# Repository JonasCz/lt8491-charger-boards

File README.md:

# LT8491 MPPT boosting solar charge controller mainboard

**PCB layout**:

**Description**: This project started out with the goal of reimplementing [Craig Peacock's design](https://circuitmaker.com/Projects/Details/Craig-Peacock-4/LT8490-Buck-Boost-Multi-Chemistry-Battery-Charger-with-MPPT) in KiCad, while also making it more compact;

**Status**: Test PCB assembled: LT8491 starts and communicates over i2C, but performance is unusably poor. Unsure why.

**Features**:

* Auxilary switching power supply to power additional future display board, can be enabled/disabled at runtime for power saving
* As compact as possible while keeping the board single sided
* High performance and efficiency (hopefully)
* XT60 connectors
* 60v max in and out

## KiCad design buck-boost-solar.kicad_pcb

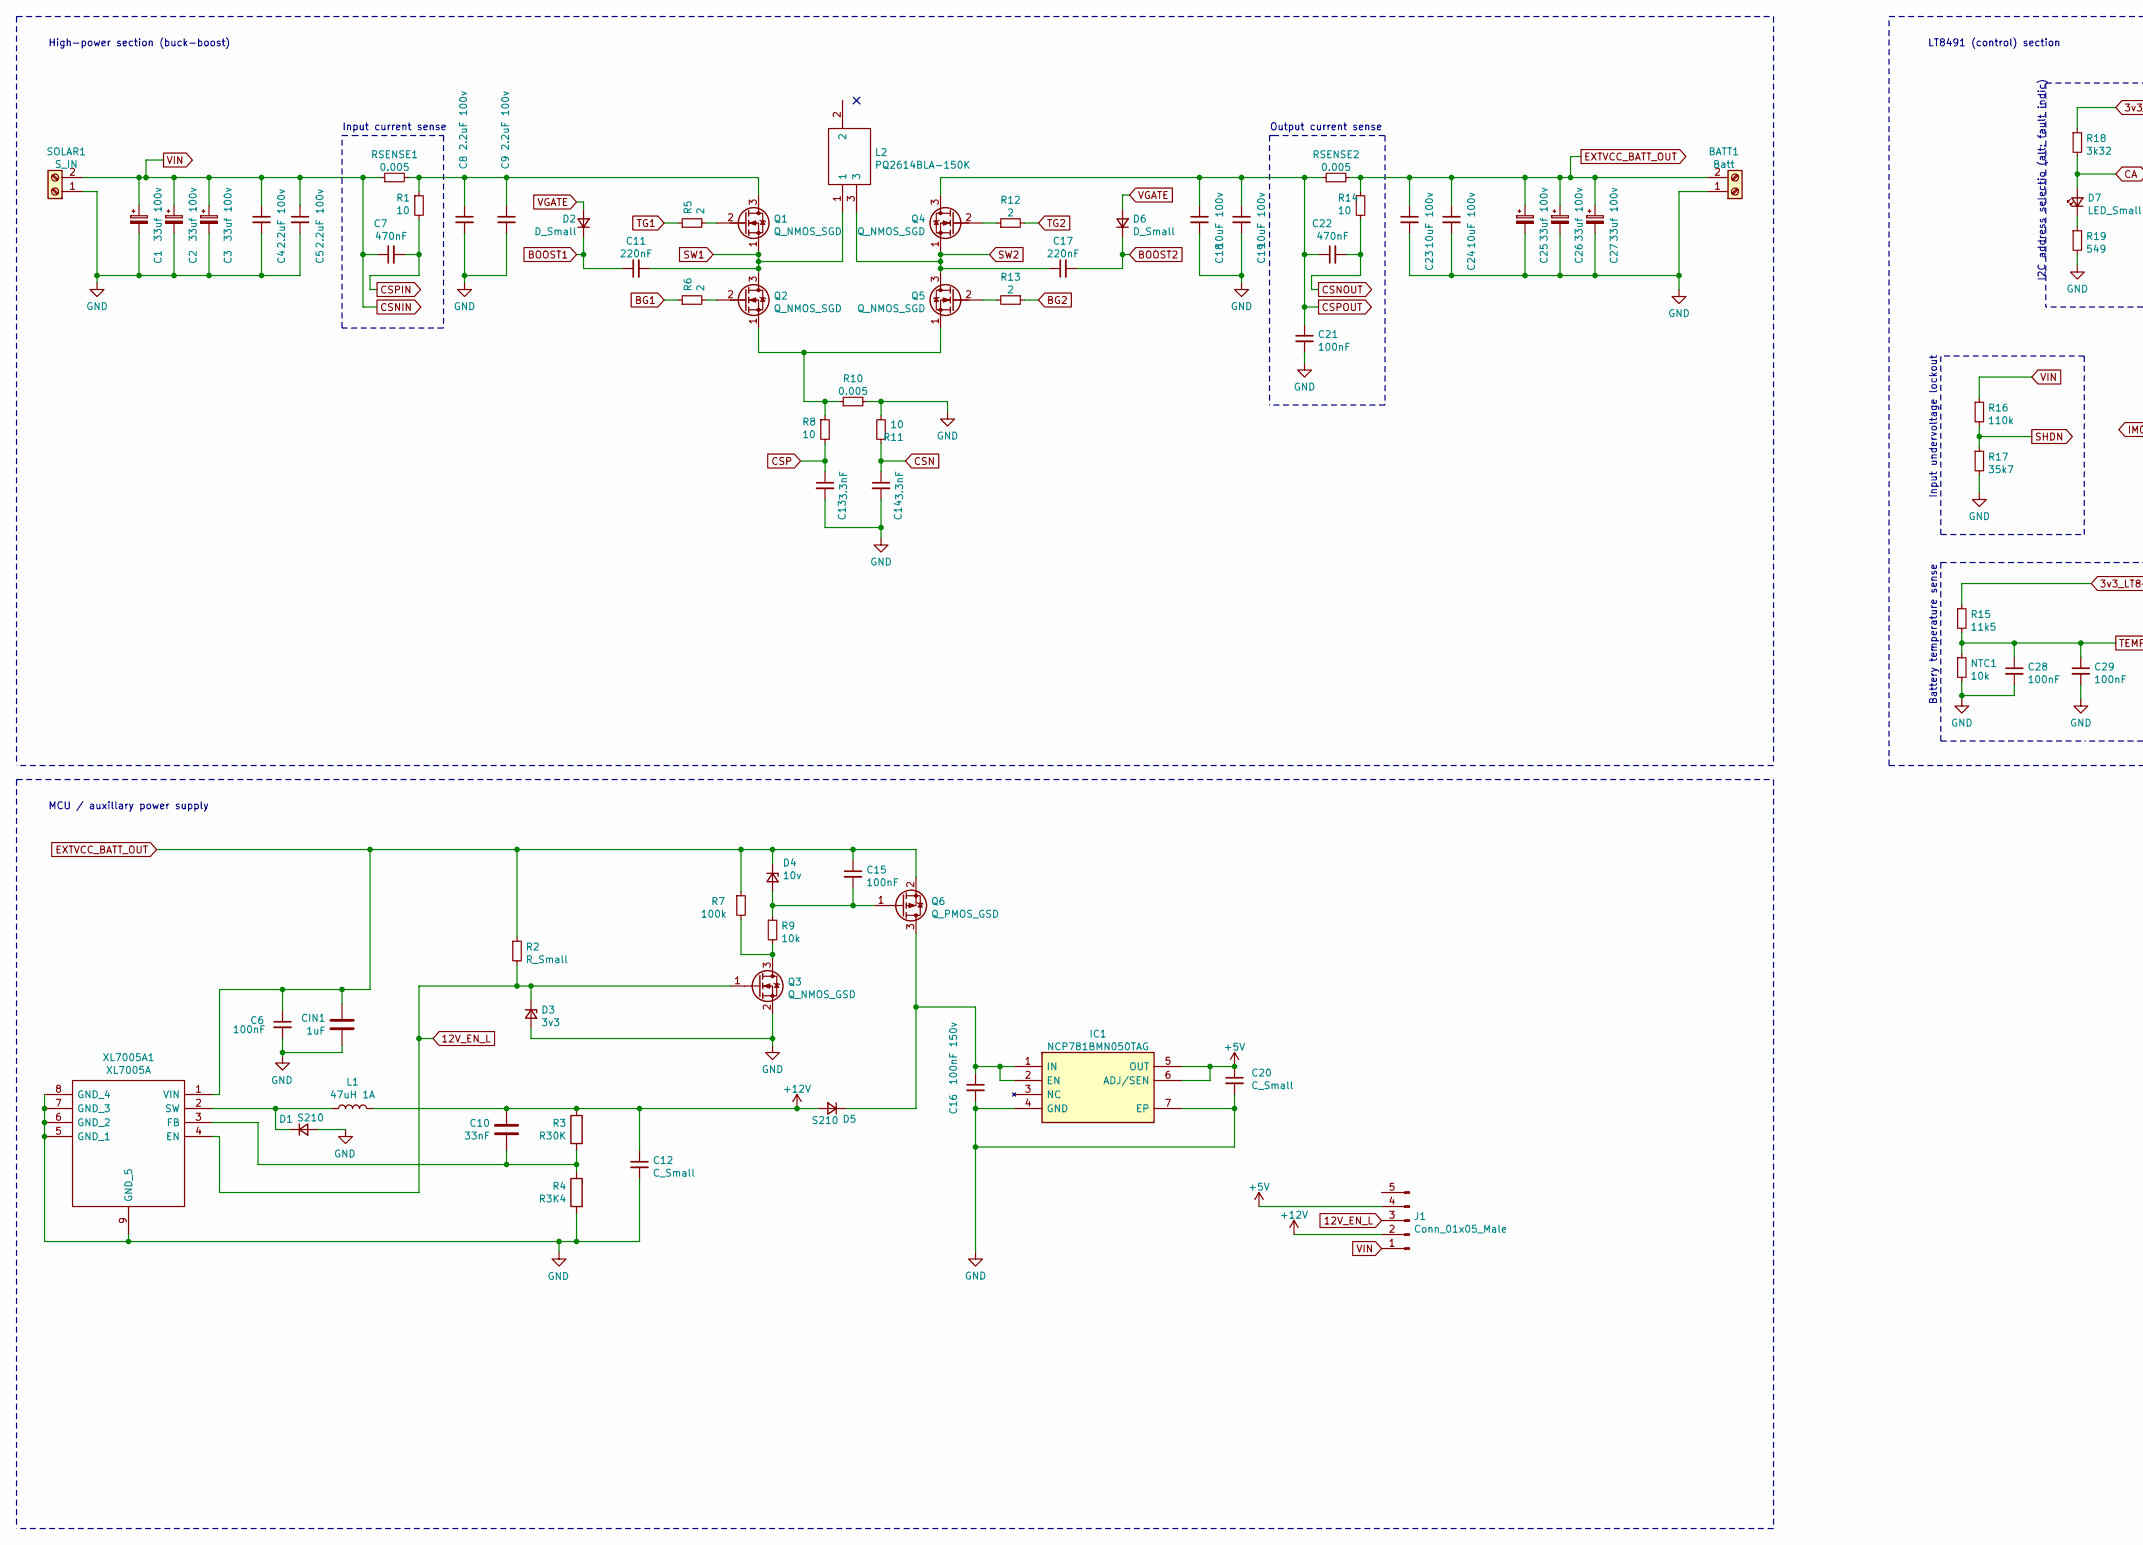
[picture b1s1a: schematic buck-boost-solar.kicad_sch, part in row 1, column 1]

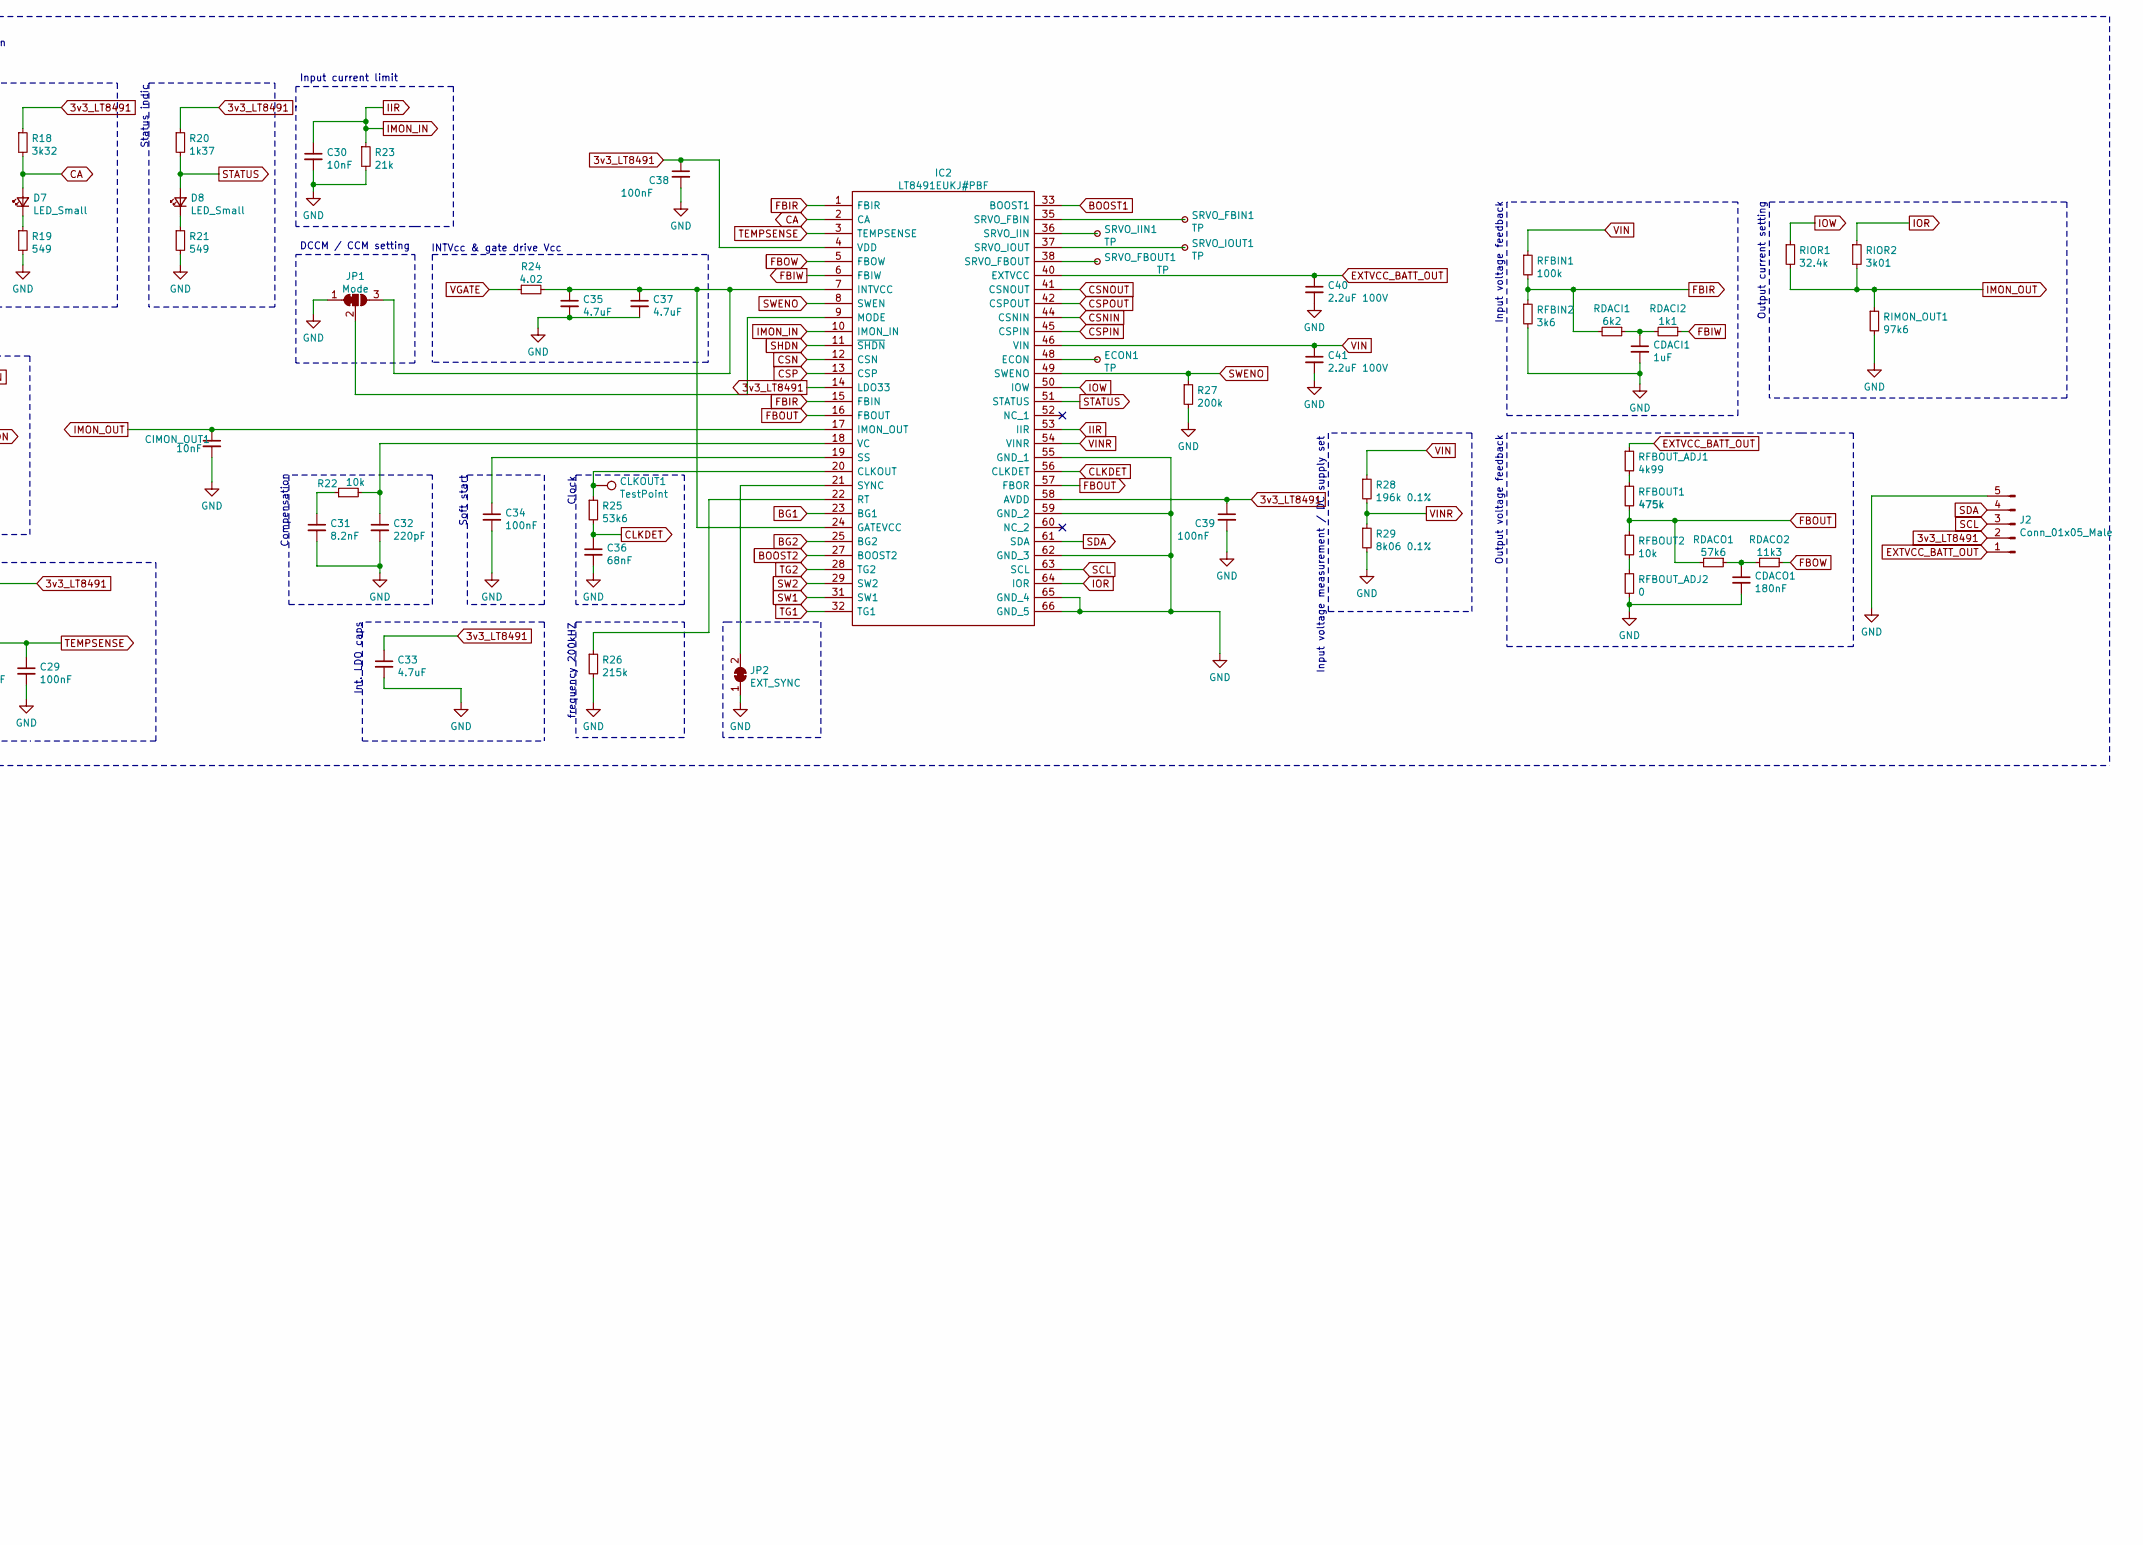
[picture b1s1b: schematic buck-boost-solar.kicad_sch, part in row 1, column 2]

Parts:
BATT1: Batt; Amass_XT60PW-M_Kombifootprint; LCSC Part Number C98732
C1, C2, C3, C25, C26, C27: 33uf 100v; CP_Radial_D10.0mm_P5.00mm; LCSC Part Number C407997
C4, C5, C8, C9: 2.2uF 100v; C_1210_3225Metric; LCSC Part Number C338133
C6, C21, C28, C29, C34, C38, C39: 100nF; C_0603_1608Metric; LCSC Part Number C696916
C7, C22: 470nF; C_0603_1608Metric; LCSC Part Number C1623
C10: 33nF; C_0603_1608Metric
C11, C17: 220nF; C_0603_1608Metric; LCSC Part Number C335532
C12: C_Small; C_1210_3225Metric
C13, C14: 3.3nF; C_0603_1608Metric; LCSC Part Number C482476
C15: 100nF; C_0603_1608Metric
C16: 100nF 150v; C_1206_3216Metric
C18, C19, C23, C24: 10uF 100v; C_2220_5650Metric; LCSC Part Number C153035
C20: C_Small; C_0603_1608Metric
C30: 10nF; C_0603_1608Metric; LCSC Part Number C100042
C31: 8.2nF; C_0603_1608Metric; LCSC Part Number C376849
C32: 220pF; C_0603_1608Metric; LCSC Part Number C376820
C33, C35, C37: 4.7uF; C_0603_1608Metric; LCSC Part Number C69335
C36: 68nF; C_0603_1608Metric; LCSC Part Number C237232
C40, C41: 2.2uF 100V; C_1210_3225Metric; LCSC Part Number C338133
CDACI1: 1uF; C_0603_1608Metric; LCSC Part Number C5673
CDACO1: 180nF; C_0603_1608Metric; LCSC Part Number C519442
CIMON_OUT1: 10nF; C_0603_1608Metric; LCSC Part Number C100042
CIN1: 1uF; C_1206_3216Metric
CLKOUT1: TestPoint; TestPoint_Pad_D1.0mm
D1, D5: S210; D_SOD-123
D2, D6: D_Small; D_SOD-123; LCSC Part Number C258207
D3: 3v3; D_SOD-123
D4: 10v; D_SOD-123
D7, D8: LED_Small; D_0805_2012Metric; LCSC Part Number C72037
ECON1: TP; TestPoint_Pad_D1.0mm
IC1: NCP781BMN050TAG; Manufacturer_Part_Number NCP781BMN050TAG; Mouser Part Number 863-NCP781BMN050TAG
IC2: LT8491EUKJ#PBF; LT8491EUKJ; Manufacturer_Part_Number LT8491EUKJ#PBF; Mouser Part Number 584-LT8491EUKJ#PBF
J1, J2: Conn_01x05_Male; PinHeader_1x05_P2.54mm_Vertical
JP1: Mode; SolderJumper-3_P1.3mm_Bridged2Bar12_RoundedPad1.0x1.5mm
JP2: EXT_SYNC; SolderJumper-2_P1.3mm_Bridged_RoundedPad1.0x1.5mm
L1: 47uH 1A; L_7.3x7.3_H4.5
L2: PQ2614BLA-150K; PQ2614BLA100K; Manufacturer_Part_Number PQ2614BLA-150K; Mouser Part Number 652-PQ2614BLA-150K
NTC1: 10k; R_0805_2012Metric; LCSC Part Number C338623
Q1, Q2, Q4, Q5: Q_NMOS_SGD; TDSON-8-1-SGD; LCSC Part Number C148260
Q3: Q_NMOS_GSD; SOT-23; LCSC Part Number C397175
Q6: Q_PMOS_GSD; SOT-23; LCSC Part Number C700960
R1, R8, R11, R14: 10; R_0603_1608Metric; LCSC Part Number C384297
R2: R_Small; R_0603_1608Metric
R3: R30K; R_0603_1608Metric
R4: R3K4; R_0603_1608Metric
R5, R6, R12, R13: 2; R_0603_1608Metric; LCSC Part Number C286596
R7: 100k; R_0603_1608Metric
R9: 10k; R_0603_1608Metric
R10: 0.005; R_2512_6332Metric; LCSC Part Number C457120
R15: 11k5; R_0603_1608Metric; LCSC Part Number C25949
R16: 110k; R_0603_1608Metric; LCSC Part Number C25805
R17: 35k7; R_0603_1608Metric; LCSC Part Number C23027
R18: 3k32; R_0603_1608Metric; LCSC Part Number C321860
R19, R21: 549; R_0603_1608Metric; LCSC Part Number C23079
R20: 1k37; R_0603_1608Metric; LCSC Part Number C22839
R22: 10k; R_0603_1608Metric; LCSC Part Number C25804
R23: 21k; R_0603_1608Metric; LCSC Part Number C22956
R24: 4.02; R_0603_1608Metric; LCSC Part Number C322168
R25: 53k6; R_0603_1608Metric; LCSC Part Number C23074
R26: 215k; R_0603_1608Metric; LCSC Part Number C22954
R27: 200k; R_0603_1608Metric; LCSC Part Number C304068
R28: 196k 0.1%; R_0603_1608Metric; LCSC Part Number C705733
R29: 8k06 0.1%; R_0603_1608Metric; LCSC Part Number C304068
RDACI1: 6k2; R_0603_1608Metric; LCSC Part Number C319499
RDACI2: 1k1; R_0603_1608Metric; LCSC Part Number C351674
RDACO1: 57k6; R_0603_1608Metric; LCSC Part Number C243028
RDACO2: 11k3; R_0603_1608Metric; LCSC Part Number C491110
RFBIN1: 100k; R_0603_1608Metric; LCSC Part Number C335088
RFBIN2: 3k6; R_0603_1608Metric; LCSC Part Number C318132
RFBOUT1: 475k; R_0603_1608Metric; LCSC Part Number C503464
RFBOUT2: 10k; R_0603_1608Metric; LCSC Part Number C309083
RFBOUT_ADJ1: 4k99; R_0603_1608Metric; LCSC Part Number C335079
RFBOUT_ADJ2: 0; R_0603_1608Metric; LCSC Part Number C286596
RIMON_OUT1: 97k6; R_0603_1608Metric; LCSC Part Number C23269
RIOR1: 32.4k; R_0603_1608Metric; LCSC Part Number C170561
RIOR2: 3k01; R_0603_1608Metric; LCSC Part Number C168308
RSENSE1, RSENSE2: 0.005; R_2512_6332Metric; LCSC Part Number C457120
SOLAR1: S_IN; Amass_XT60PW-M_Kombifootprint; LCSC Part Number C428722
SRVO_FBIN1: TP; TestPoint_Pad_D1.0mm
SRVO_FBOUT1: TP; TestPoint_Pad_D1.0mm
SRVO_IIN1: TP; TestPoint_Pad_D1.0mm
SRVO_IOUT1: TP; TestPoint_Pad_D1.0mm
XL7005A1: XL7005A; SOIC127P600X175-9N; Manufacturer_Part_Number XL7005A; LCSC Part Number C50848

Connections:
3v3_LT8491: C33.1, C38.1, C39.1, IC2.4 (VDD), IC2.14 (LDO33), IC2.58 (AVDD), J2.2, R15.1, R18.1, R20.1
12V_EN_L: D3.1 (K), J1.3, Q3.1 (G), R2.2, XL7005A1.4 (EN)
+5V: C20.1, IC1.5 (OUT), IC1.6 (ADJ/SEN), J1.4
+12V: C10.1, C12.1, D5.2 (A), J1.2, L1.1, R3.1
BG1: IC2.23 (BG1), R6.1
BG2: IC2.25 (BG2), R13.1
BOOST1: C11.1, D2.1 (K), IC2.33 (BOOST1)
BOOST2: C17.2, D6.1 (K), IC2.27 (BOOST2)
CA: D7.2 (A), IC2.2 (CA), R18.2
CLKDET: C36.1, IC2.56 (CLKDET), R25.2
CSN: C14.1, IC2.12 (CSN), R11.1
CSNIN: C1.1, C2.1, C3.1, C4.1, C5.1, C7.1, C41.1, IC2.44 (CSNIN), IC2.46 (VIN), J1.1, R16.1, R28.1, RFBIN1.1, RSENSE1.1, SOLAR1.2
CSNOUT: C22.2, IC2.41 (CSNOUT), R14.2
CSP: C13.1, IC2.13 (CSP), R8.2
CSPIN: C7.2, IC2.45 (CSPIN), R1.2
CSPOUT: C18.1, C19.1, C21.1, C22.1, IC2.42 (CSPOUT), Q4.3 (D), RSENSE2.1
EXTVCC_BATT_OUT: BATT1.2, C6.1, C15.1, C23.1, C24.1, C25.1, C26.1, C27.1, C40.1, CIN1.1, D4.1 (K), IC2.40 (EXTVCC), J2.1, Q6.2 (S), R2.1, R7.1, R14.1, RFBOUT_ADJ1.1, RSENSE2.2, XL7005A1.1 (VIN)
FBIR: IC2.1 (FBIR), IC2.15 (FBIN), RDACI1.2, RFBIN1.2, RFBIN2.1
FBIW: IC2.6 (FBIW), RDACI2.1
FBOUT: IC2.16 (FBOUT), IC2.57 (FBOR), RDACO1.2, RFBOUT1.2, RFBOUT2.1
FBOW: IC2.5 (FBOW), RDACO2.1
GND: BATT1.1, C1.2, C2.2, C3.2, C4.2, C5.2, C6.2, C8.2, C9.2, C12.2, C13.2, C14.2, C16.2, C18.2, C19.2, C20.2, C21.2, C23.2, C24.2, C25.2, C26.2, C27.2, C28.2, C29.2, C30.2, C31.2, C32.2, C33.2, C34.2, C35.2, C36.2, C37.2, C38.2, C39.2, C40.2, C41.2, CDACI1.2, CDACO1.2, CIMON_OUT1.2, CIN1.2, D1.2 (A), D3.2 (A), IC1.4 (GND), IC1.7 (EP), IC2.55 (GND_1), IC2.59 (GND_2), IC2.62 (GND_3), IC2.65 (GND_4), IC2.66 (GND_5), J2.5, JP1.1 (A), JP2.1 (A), NTC1.2, Q3.2 (S), R4.2, R10.2, R11.2, R17.2, R19.2, R21.2, R23.2, R26.2, R27.2, R29.2, RFBIN2.2, RFBOUT_ADJ2.2, RIMON_OUT1.2, SOLAR1.1, XL7005A1.5 (GND_1), XL7005A1.6 (GND_2), XL7005A1.7 (GND_3), XL7005A1.8 (GND_4), XL7005A1.9 (GND_5)
IIR: C30.1, IC2.10 (IMON_IN), IC2.53 (IIR), R23.1
IMON_OUT: CIMON_OUT1.1, IC2.17 (IMON_OUT), RIMON_OUT1.1, RIOR1.2, RIOR2.2
IOR: IC2.64 (IOR), RIOR2.1
IOW: IC2.50 (IOW), RIOR1.1
unnamed: C8.1, C9.1, Q1.3 (D), R1.1, RSENSE1.2
unnamed: C10.2, R3.2, R4.1, XL7005A1.3 (FB)
unnamed: C15.2, D4.2 (A), Q6.1 (G), R9.1
unnamed: C31.1, R22.1
unnamed: C32.1, IC2.18 (VC), R22.2
unnamed: C34.1, IC2.19 (SS)
unnamed: C35.1, C37.1, IC2.7 (INTVCC), IC2.24 (GATEVCC), JP1.3 (B), R24.2
unnamed: CDACI1.1, RDACI1.1, RDACI2.2
unnamed: CDACO1.1, RDACO1.1, RDACO2.2
unnamed: CLKOUT1.1, IC2.20 (CLKOUT), R25.1
unnamed: D1.1 (K), L1.2, XL7005A1.2 (SW)
unnamed: C16.1, D5.1 (K), IC1.1 (IN), IC1.2 (EN), Q6.3 (D)
unnamed: D7.1 (K), R19.1
unnamed: D8.1 (K), R21.1
unnamed: ECON1.1, IC2.48 (ECON)
unnamed: IC2.9 (MODE), JP1.2 (C)
unnamed: IC2.21 (SYNC), JP2.2 (B)
unnamed: IC2.22 (RT), R26.1
unnamed: IC2.35 (SRVO_FBIN), SRVO_FBIN1.1
unnamed: IC2.36 (SRVO_IIN), SRVO_IIN1.1
unnamed: IC2.37 (SRVO_IOUT), SRVO_IOUT1.1
unnamed: IC2.38 (SRVO_FBOUT), SRVO_FBOUT1.1
unnamed: Q1.2 (G), R5.2
unnamed: Q2.1 (S), Q5.1 (S), R8.1, R10.1
unnamed: Q2.2 (G), R6.2
unnamed: Q3.3 (D), R7.2, R9.2
unnamed: Q4.2 (G), R12.1
unnamed: Q5.2 (G), R13.2
unnamed: RFBOUT1.1, RFBOUT_ADJ1.2
unnamed: RFBOUT2.2, RFBOUT_ADJ2.1
SCL: IC2.63 (SCL), J2.3
SDA: IC2.61 (SDA), J2.4
SHDN: IC2.11 (~SHDN), R16.2, R17.1
STATUS: D8.2 (A), IC2.51 (STATUS), R20.2
SW1: C11.2, IC2.31 (SW1), L2.1, Q1.1 (S), Q2.3 (D)
SW2: C17.1, IC2.29 (SW2), L2.3, Q4.1 (S), Q5.3 (D)
SWENO: IC2.8 (SWEN), IC2.49 (SWENO), R27.1
TEMPSENSE: C28.1, C29.1, IC2.3 (TEMPSENSE), NTC1.1, R15.2
TG1: IC2.32 (TG1), R5.1
TG2: IC2.28 (TG2), R12.2
VGATE: D2.2 (A), D6.2 (A), R24.1
VINR: IC2.54 (VINR), R28.2, R29.1

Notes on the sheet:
High-power section (buck-boost)
MCU / auxillary power supply
Input current sense
Output current sense
LT8491 (control) section
Input undervoltage lockout
Battery temperature sense
I2C address selectio (alt: fault indic)
Status indic
Compensation
Input current limit
DCCM / CCM setting
Int. LDO caps
INTVcc & gate drive Vcc
Soft start
Clock
frequency 200kHZ
Input voltage measurement / DC supply set
Input voltage feedback
Output voltage feedback
Output current setting

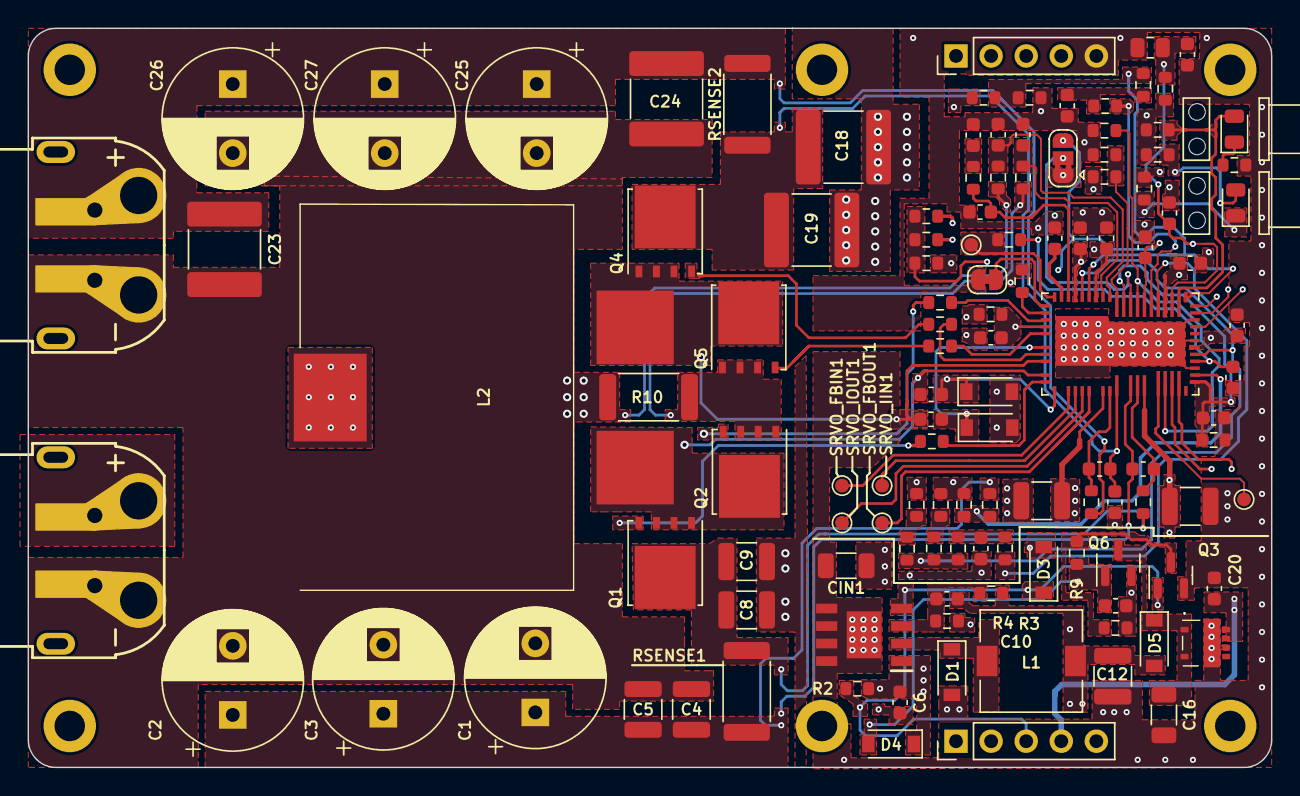
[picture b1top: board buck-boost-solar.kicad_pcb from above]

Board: 4 copper layers, 90.0 x 53.5 mm, 121 parts (0 on the bottom side), 68 nets.

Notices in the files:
parts and their libraries:
Copyright 2021 Accelerated Designs. All rights reserved.
